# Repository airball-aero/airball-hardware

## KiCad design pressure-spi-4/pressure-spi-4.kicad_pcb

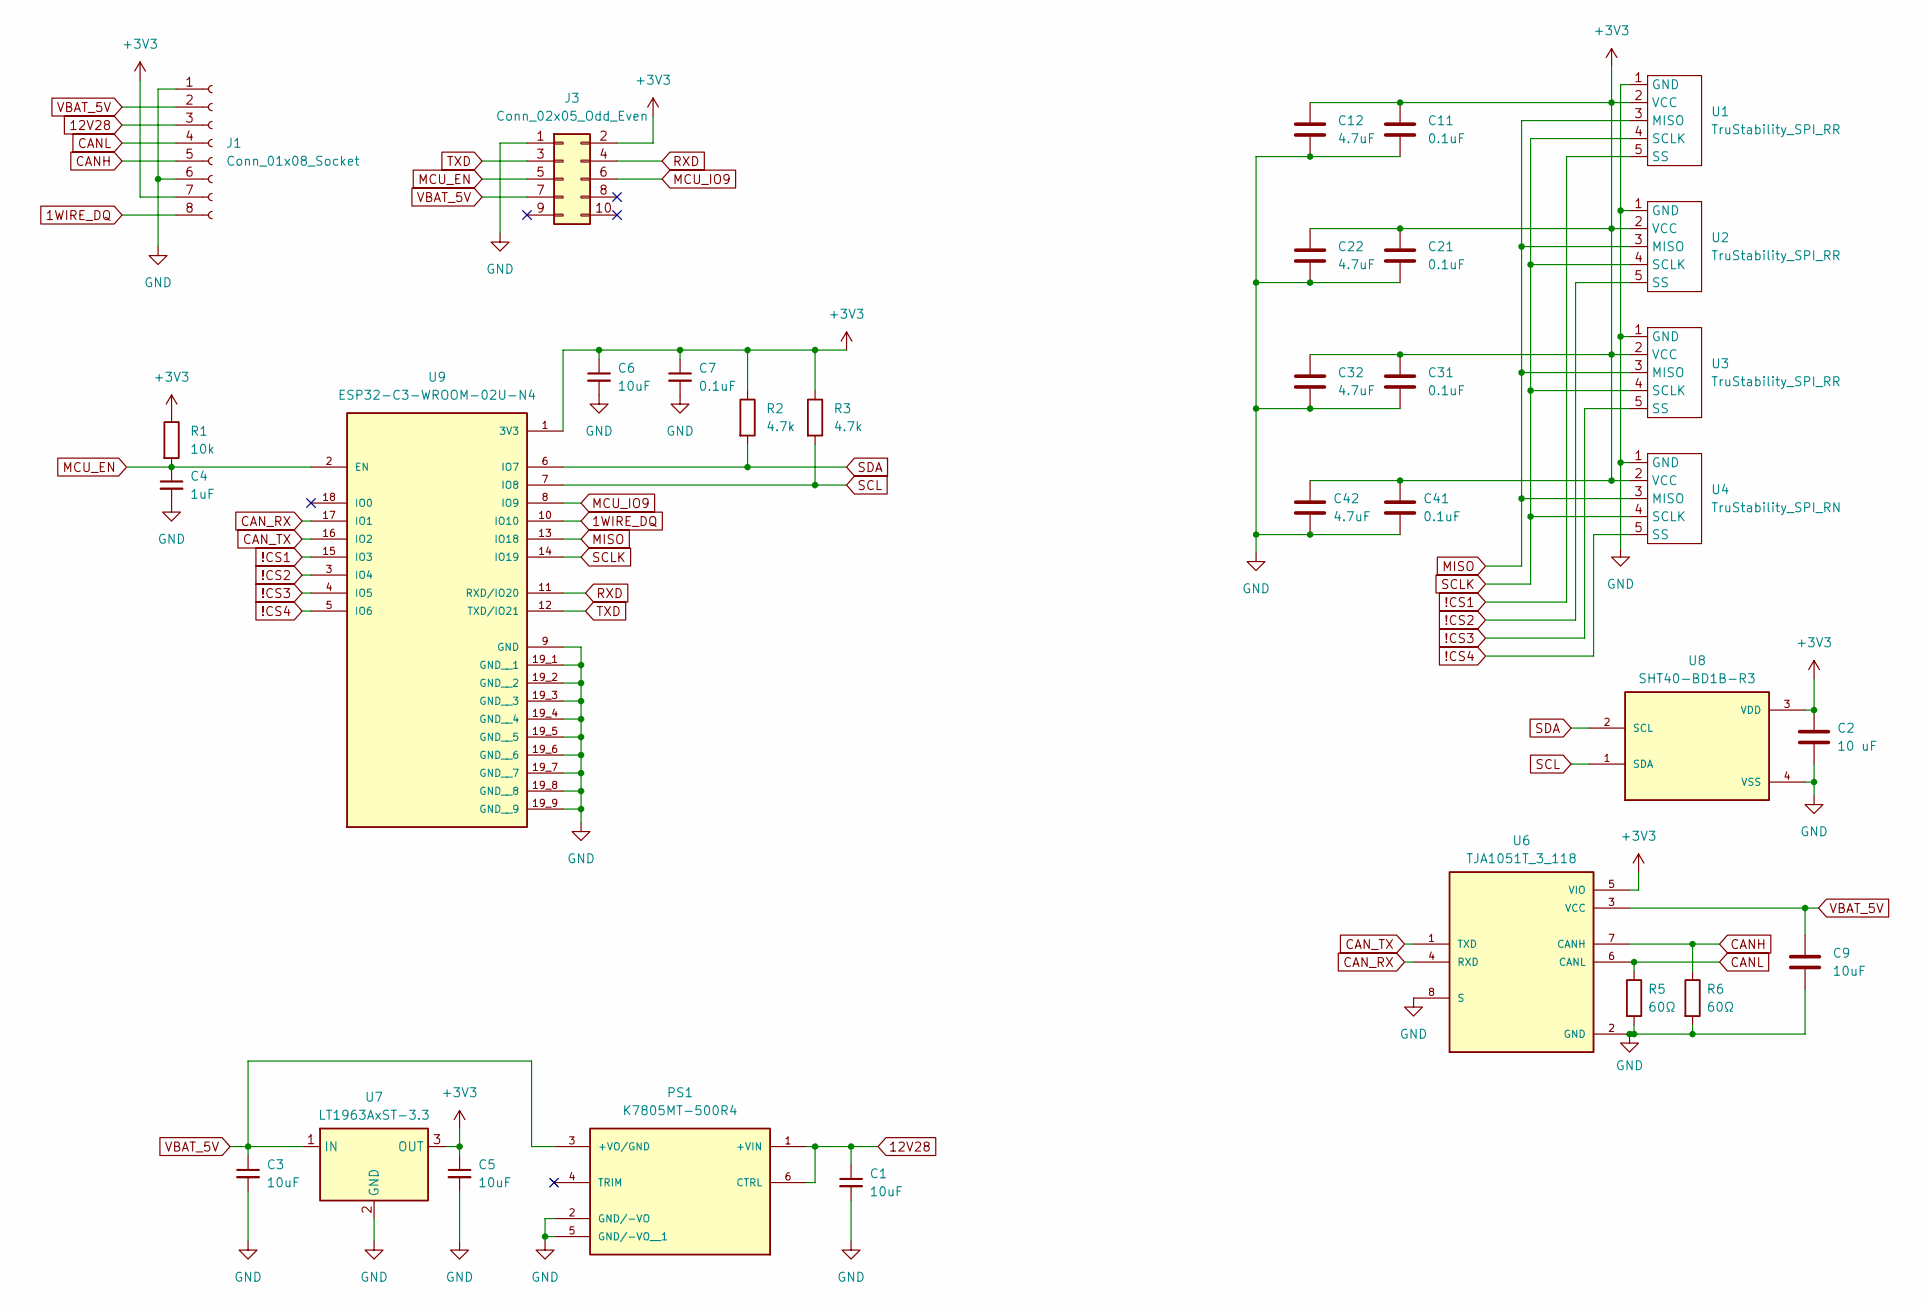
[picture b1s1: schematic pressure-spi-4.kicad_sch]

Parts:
C1, C3, C5, C6, C9: 10uF; C_0603_1608Metric
C2: 10 uF; C_0603_1608Metric
C4: 1uF; C_0603_1608Metric
C7, C11, C21, C31, C41: 0.1uF; C_0603_1608Metric
C12, C22, C32, C42: 4.7uF; C_0603_1608Metric
J1: Conn_01x08_Socket; PinHeader_1x08_P1.27mm_Vertical
J3: Conn_02x05_Odd_Even; PinHeader_2x05_P1.27mm_Vertical
PS1: K7805MT-500R4; CONV_K7805MT-500R4; PARTREV 2020.08.12-A/1
R1: 10k; R_0603_1608Metric
R2, R3: 4.7k; R_0603_1608Metric
R5, R6: 60Ω; R_0603_1608Metric
U1, U2, U3: TruStability_SPI_RR; TruStability SMT RR
U4: TruStability_SPI_RN; TruStability SMT RN
U6: TJA1051T_3_118; PARTREV 9
U7: LT1963AxST-3.3; SOT-223-3_TabPin2
U8: SHT40-BD1B-R3; SHT4X humidity sensor
U9: ESP32-C3-WROOM-02U-N4; XCVR_ESP32-C3-WROOM-02U-N4; PARTREV 1.3

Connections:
1WIRE_DQ: J1.8, U9.10 (IO10)
12V28: C1.1, J1.3, PS1.1 (+VIN), PS1.6 (CTRL)
!CS1: U1.5 (SS), U9.15 (IO3)
!CS2: U2.5 (SS), U9.3 (IO4)
!CS3: U3.5 (SS), U9.4 (IO5)
!CS4: U4.5 (SS), U9.5 (IO6)
+3V3: C2.1, C5.1, C6.1, C7.1, C11.1, C12.1, C21.1, C22.1, C31.1, C32.1, C41.1, C42.1, J1.7, J3.2, R1.1, R2.1, R3.1, U1.2 (VCC), U2.2 (VCC), U3.2 (VCC), U4.2 (VCC), U6.5 (VIO), U7.3 (OUT), U8.3 (VDD), U9.1 (3V3)
CANH: J1.5, R6.1, U6.7 (CANH)
CANL: J1.4, R5.1, U6.6 (CANL)
CAN_RX: U6.4 (RXD), U9.17 (IO1)
CAN_TX: U6.1 (TXD), U9.16 (IO2)
GND: C1.2, C2.2, C3.2, C4.2, C5.2, C6.2, C7.2, C9.2, C11.2, C12.2, C21.2, C22.2, C31.2, C32.2, C41.2, C42.2, J1.1, J1.6, J3.1, PS1.2 (GND/-VO), PS1.5 (GND/-VO__1), R5.2, R6.2, U1.1 (GND), U2.1 (GND), U3.1 (GND), U4.1 (GND), U6.2 (GND), U6.8 (S), U7.2 (GND), U8.4 (VSS), U9.9 (GND), U9.19_1 (GND__1), U9.19_2 (GND__2), U9.19_3 (GND__3), U9.19_4 (GND__4), U9.19_5 (GND__5), U9.19_6 (GND__6), U9.19_7 (GND__7), U9.19_8 (GND__8), U9.19_9 (GND__9), U9.20_1, U9.20_2, U9.20_3, U9.20_4, U9.20_5, U9.20_6, U9.20_7, U9.20_8, U9.20_9, U9.20_10, U9.20_11, U9.20_12
MCU_EN: C4.1, J3.5, R1.2, U9.2 (EN)
MCU_IO9: J3.6, U9.8 (IO9)
MISO: U1.3 (MISO), U2.3 (MISO), U3.3 (MISO), U4.3 (MISO), U9.13 (IO18)
RXD: J3.4, U9.11 (RXD/IO20)
SCL: R3.2, U8.1 (SDA), U9.7 (IO8)
SCLK: U1.4 (SCLK), U2.4 (SCLK), U3.4 (SCLK), U4.4 (SCLK), U9.14 (IO19)
SDA: R2.2, U8.2 (SCL), U9.6 (IO7)
TXD: J3.3, U9.12 (TXD/IO21)
VBAT_5V: C3.1, C9.1, J1.2, J3.7, PS1.3 (+VO/GND), U6.3 (VCC), U7.1 (IN)

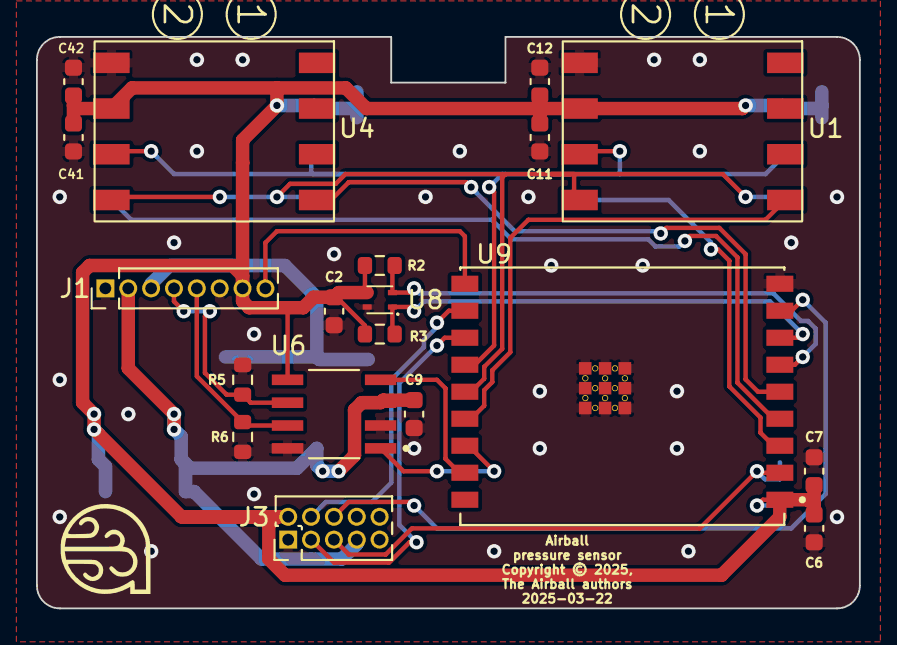
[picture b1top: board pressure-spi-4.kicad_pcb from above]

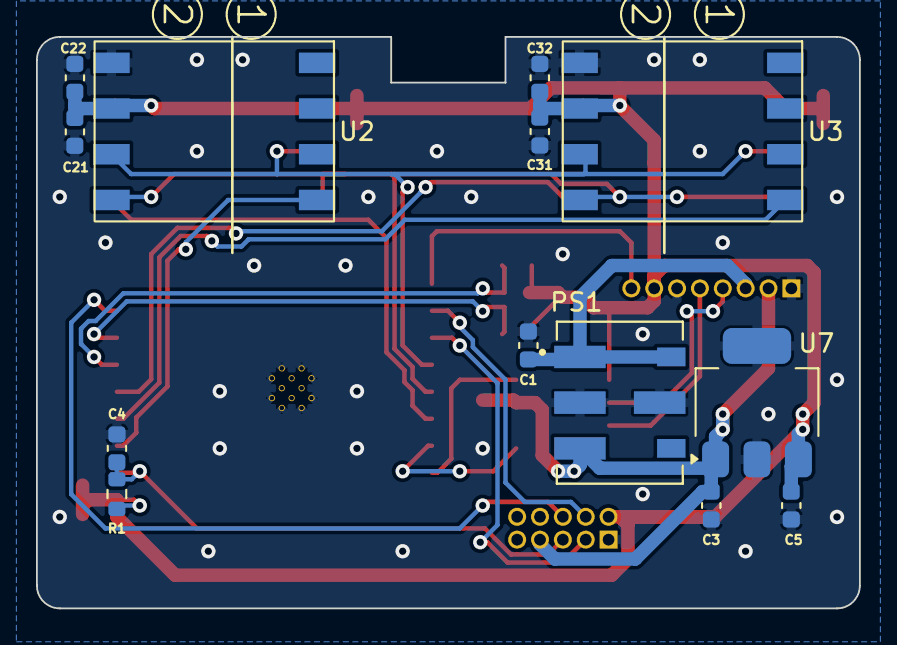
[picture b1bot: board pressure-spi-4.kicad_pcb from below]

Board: 2 copper layers, 45.7 x 31.8 mm, 32 parts (13 on the bottom side), 21 nets.

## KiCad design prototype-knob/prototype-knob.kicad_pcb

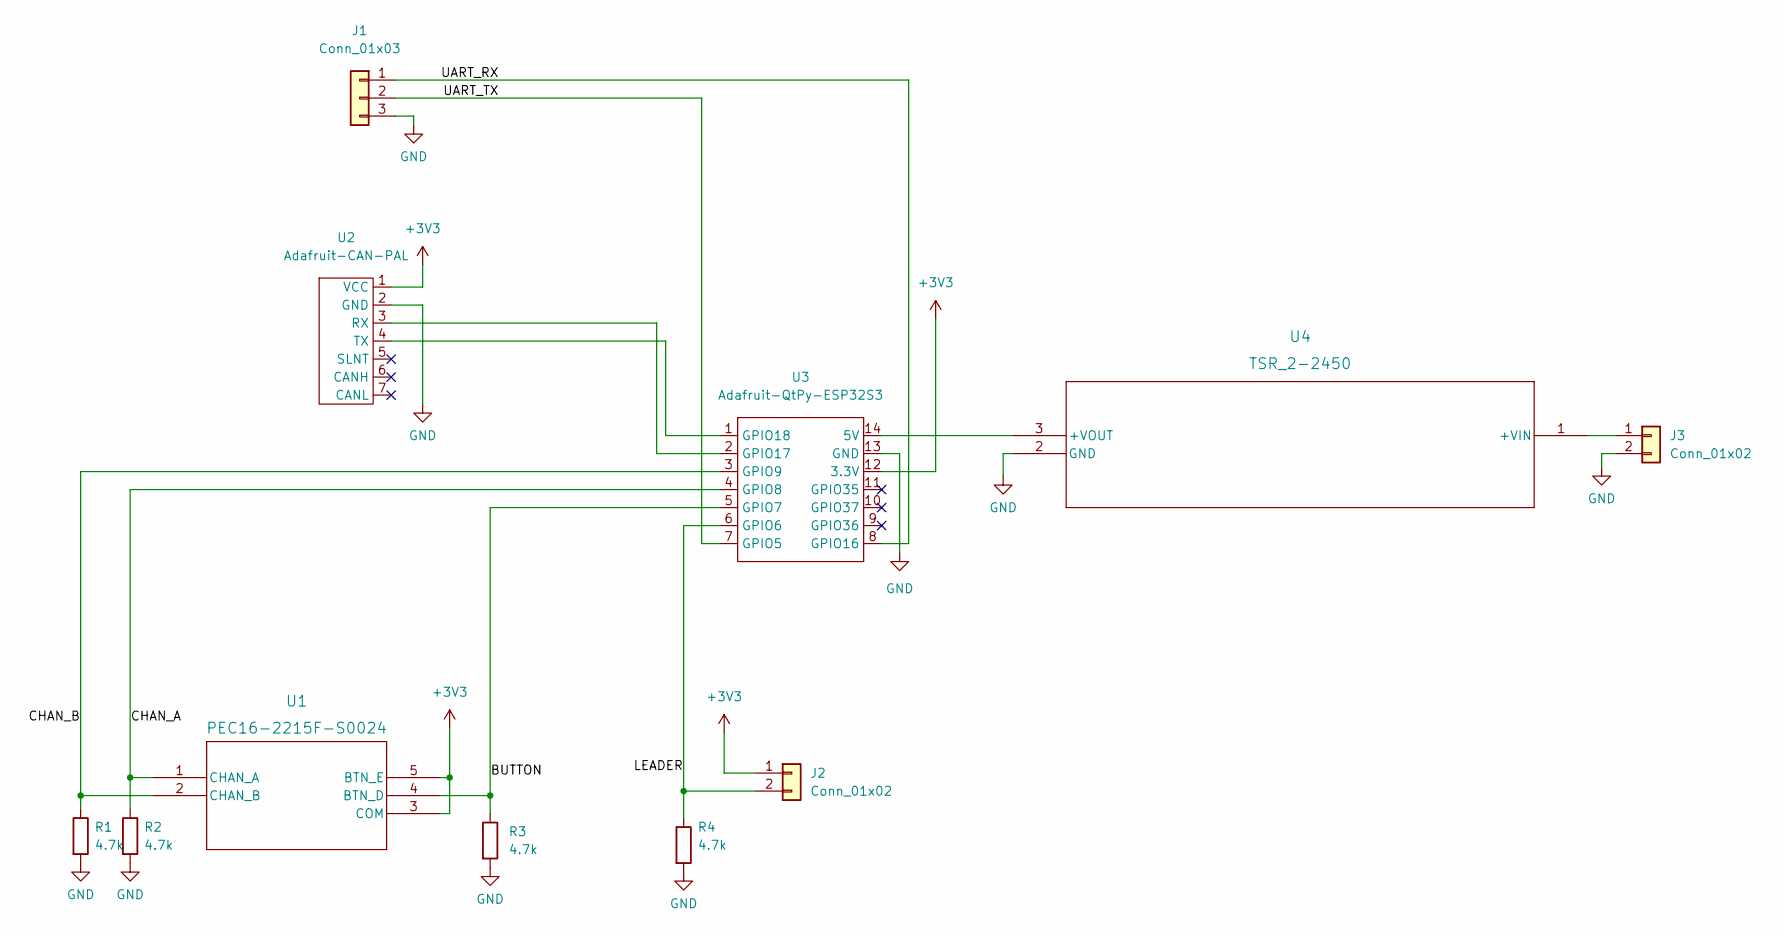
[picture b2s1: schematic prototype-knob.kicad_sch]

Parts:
J1: Conn_01x03; PinHeader_1x03_P2.54mm_Vertical
J2, J3: Conn_01x02; PinHeader_1x02_P2.54mm_Vertical
R1, R2, R3, R4: 4.7k; R_Axial_DIN0207_L6.3mm_D2.5mm_P10.16mm_Horizontal
U1: PEC16-2215F-S0024; PEC16-2215F_BRN
U2: Adafruit-CAN-PAL
U3: Adafruit-QtPy-ESP32S3
U4: TSR_2-2450; TSR 2-2450_TRP

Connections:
+3V3: J2.1, U1.3 (COM), U1.5 (BTN_E), U2.1 (VCC), U3.12 (3.3V)
/BUTTON: R3.1, U1.4 (BTN_D), U3.5 (GPIO7)
/CHAN_A: R2.1, U1.1 (CHAN_A), U3.4 (GPIO8)
/CHAN_B: R1.1, U1.2 (CHAN_B), U3.3 (GPIO9)
/LEADER: J2.2, R4.1, U3.6 (GPIO6)
/UART_RX: J1.1, U3.8 (GPIO16)
/UART_TX: J1.2, U3.7 (GPIO5)
GND: J1.3, J3.2, R1.2, R2.2, R3.2, R4.2, U2.2 (GND), U3.13 (GND), U4.2 (GND)
unnamed: J3.1, U4.1 (+VIN)
unnamed: U2.3 (RX), U3.2 (GPIO17)
unnamed: U2.4 (TX), U3.1 (GPIO18)
unnamed: U3.14 (5V), U4.3 (+VOUT)

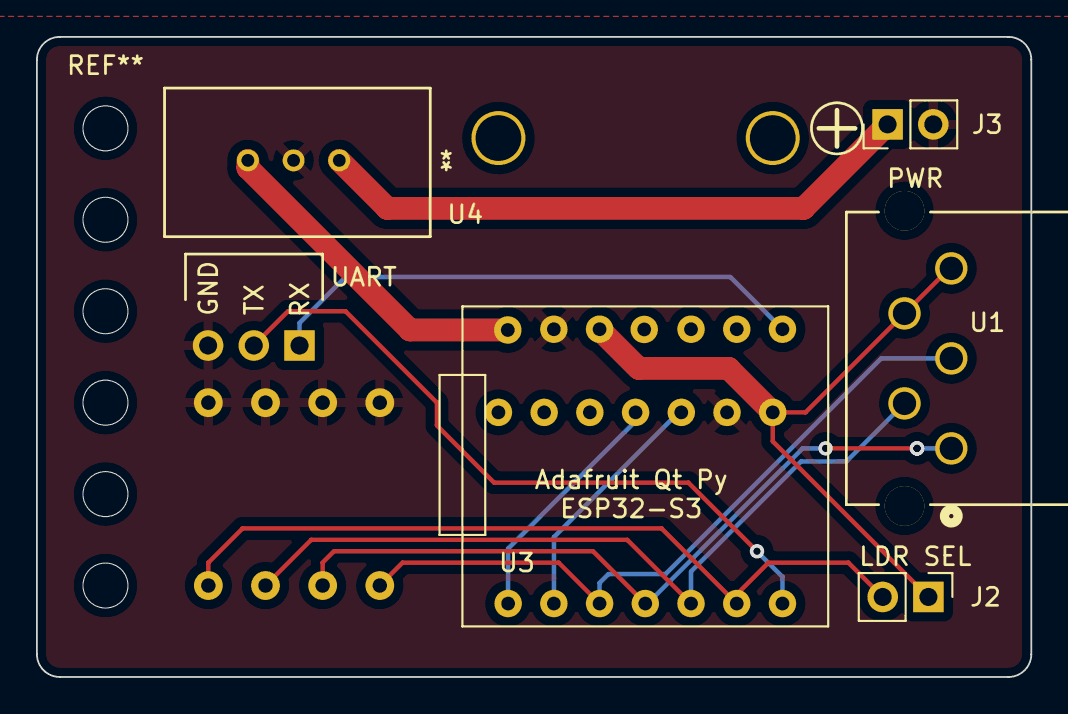
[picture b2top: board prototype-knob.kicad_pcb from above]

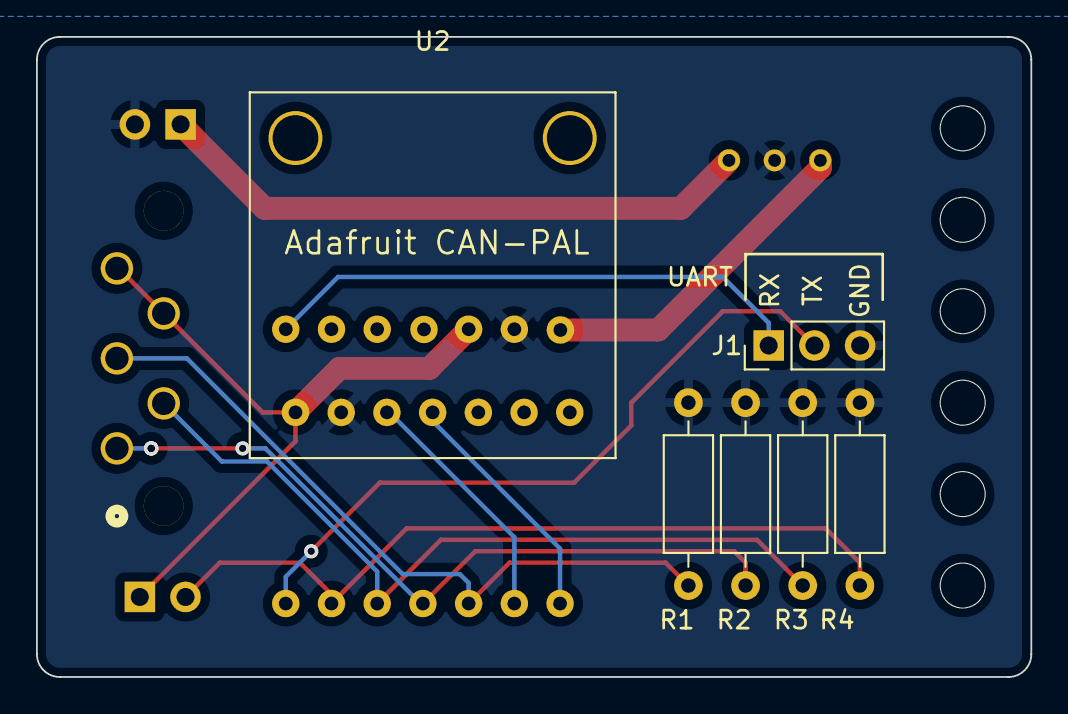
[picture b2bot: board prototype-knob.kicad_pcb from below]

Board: 2 copper layers, 55.2 x 35.6 mm, 11 parts (6 on the bottom side), 12 nets.

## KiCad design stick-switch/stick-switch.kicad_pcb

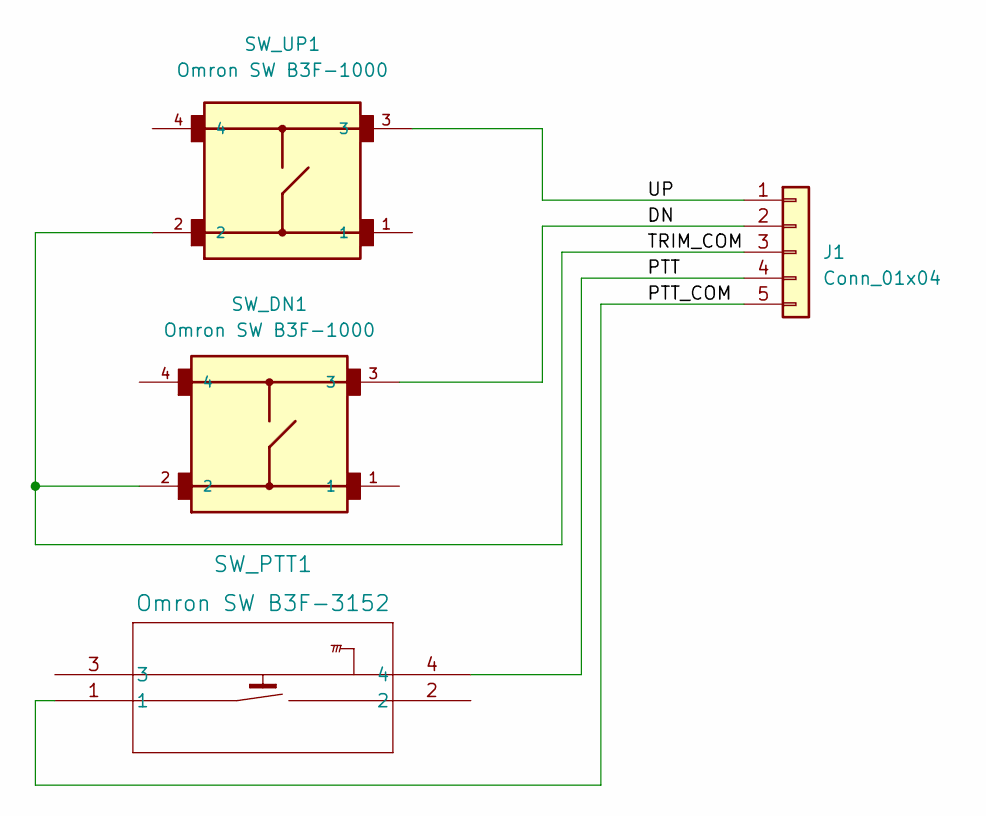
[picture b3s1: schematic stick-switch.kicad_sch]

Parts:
J1: Conn_01x04; PinHeader_1x05_P1.27mm_Vertical
SW_DN1: Omron SW B3F-1000
SW_PTT1: Omron SW B3F-3152
SW_UP1: Omron SW B3F-1000

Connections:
/DN: J1.2, SW_DN1.3
/PTT: J1.4, SW_PTT1.4
/PTT_COM: J1.5, SW_PTT1.1
/TRIM_COM: J1.3, SW_DN1.2, SW_UP1.2
/UP: J1.1, SW_UP1.3

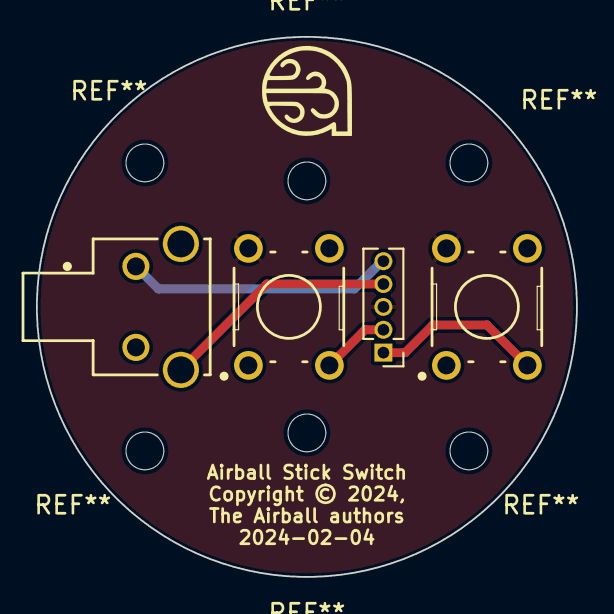
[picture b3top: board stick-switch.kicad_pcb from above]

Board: 2 copper layers, 30.0 x 30.0 mm, 4 parts (0 on the bottom side), 5 nets.

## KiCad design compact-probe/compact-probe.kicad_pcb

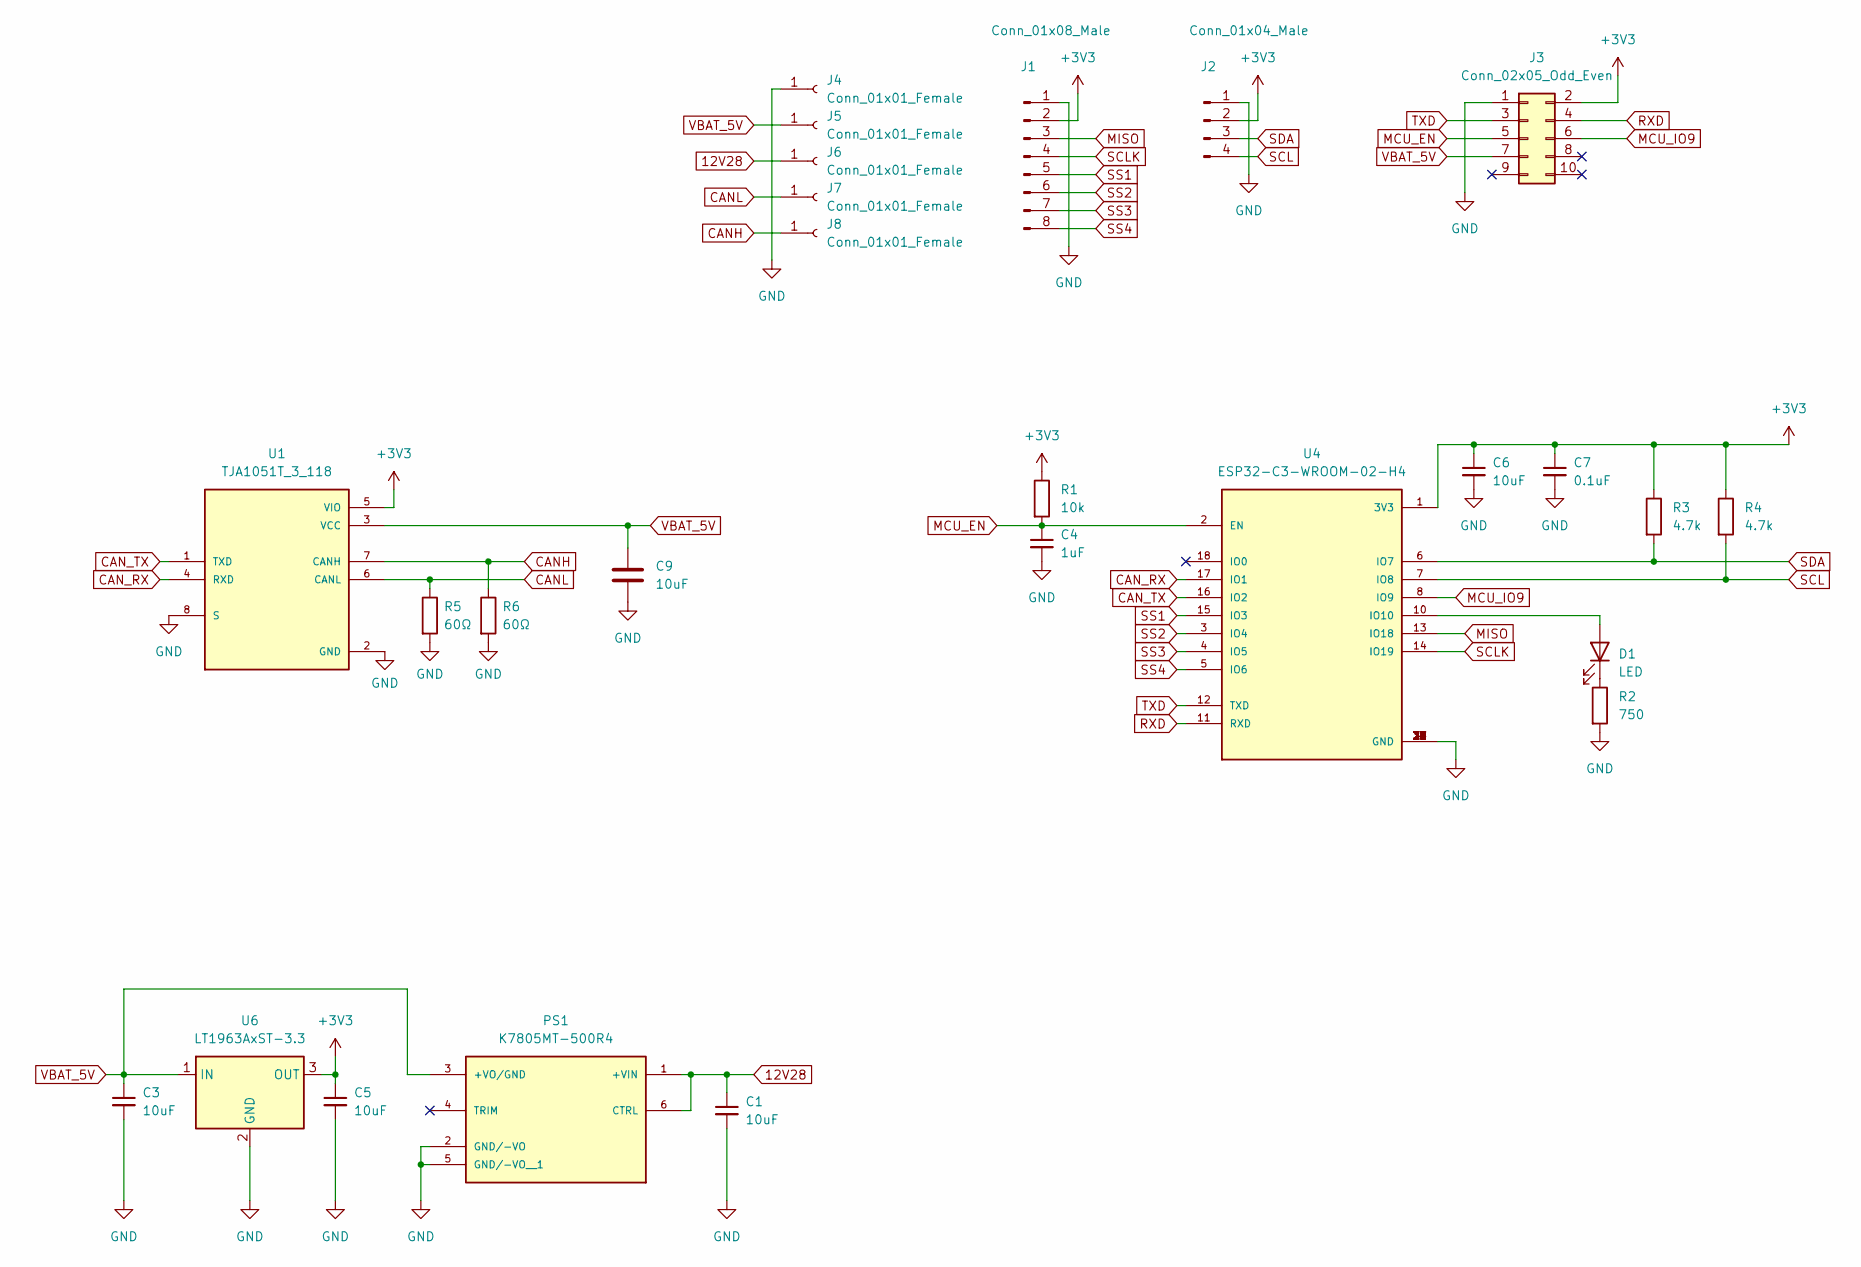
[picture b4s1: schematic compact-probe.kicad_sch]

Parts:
C1, C3, C5, C6, C9: 10uF; C_0603_1608Metric
C4: 1uF; C_0603_1608Metric
C7: 0.1uF; C_0603_1608Metric
D1: LED; LED_0603_1608Metric
J1: Conn_01x08_Male; JST_SH_SM08B-SRSS-TB_1x08-1MP_P1.00mm_Horizontal
J2: Conn_01x04_Male; JST_SM04B-SRSS-TB(LF)(SN)
J3: Conn_02x05_Odd_Even; PinHeader_2x05_P1.27mm_Vertical
J4, J5, J6, J7, J8: Conn_01x01_Female; SolderWirePad_1x01_SMD_1x2mm
PS1: K7805MT-500R4; CONV_K7805MT-500R4; PARTREV 2020.08.12-A/1
R1: 10k; R_0603_1608Metric
R2: 750; R_0603_1608Metric
R3, R4: 4.7k; R_0603_1608Metric
R5, R6: 60Ω; R_0603_1608Metric
U1: TJA1051T_3_118; PARTREV 9
U4: ESP32-C3-WROOM-02-H4; MODULE_ESP32-C3-WROOM-02-H4
U6: LT1963AxST-3.3; SOT-223-3_TabPin2

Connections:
12V28: C1.1, J6.1, PS1.1 (+VIN), PS1.6 (CTRL)
+3V3: C5.1, C6.1, C7.1, J1.2, J2.2, J3.2, R1.1, R3.1, R4.1, U1.5 (VIO), U4.1 (3V3), U6.3 (OUT)
CANH: J8.1, R6.1, U1.7 (CANH)
CANL: J7.1, R5.1, U1.6 (CANL)
CAN_RX: U1.4 (RXD), U4.17 (IO1)
CAN_TX: U1.1 (TXD), U4.16 (IO2)
GND: C1.2, C3.2, C4.2, C5.2, C6.2, C7.2, C9.2, J1.1, J2.1, J3.1, J4.1, PS1.2 (GND/-VO), PS1.5 (GND/-VO__1), R2.2, R5.2, R6.2, U1.2 (GND), U1.8 (S), U4.9 (GND), U4.19 (GND), U4.20 (GND), U4.21 (GND), U4.22 (GND), U4.23 (GND), U4.24 (GND), U4.25 (GND), U4.26 (GND), U4.27 (GND), U4.28 (GND), U4.29 (GND), U4.30 (GND), U4.31 (GND), U4.32 (GND), U4.33 (GND), U4.34 (GND), U4.35 (GND), U4.36 (GND), U4.37 (GND), U4.38 (GND), U4.39 (GND), U6.2 (GND)
MCU_EN: C4.1, J3.5, R1.2, U4.2 (EN)
MCU_IO9: J3.6, U4.8 (IO9)
MISO: J1.3, U4.13 (IO18)
unnamed: D1.1 (K), R2.1
unnamed: D1.2 (A), U4.10 (IO10)
RXD: J3.4, U4.11 (RXD)
SCL: J2.4, R4.2, U4.7 (IO8)
SCLK: J1.4, U4.14 (IO19)
SDA: J2.3, R3.2, U4.6 (IO7)
SS1: J1.5, U4.15 (IO3)
SS2: J1.6, U4.3 (IO4)
SS3: J1.7, U4.4 (IO5)
SS4: J1.8, U4.5 (IO6)
TXD: J3.3, U4.12 (TXD)
VBAT_5V: C3.1, C9.1, J3.7, J5.1, PS1.3 (+VO/GND), U1.3 (VCC), U6.1 (IN)

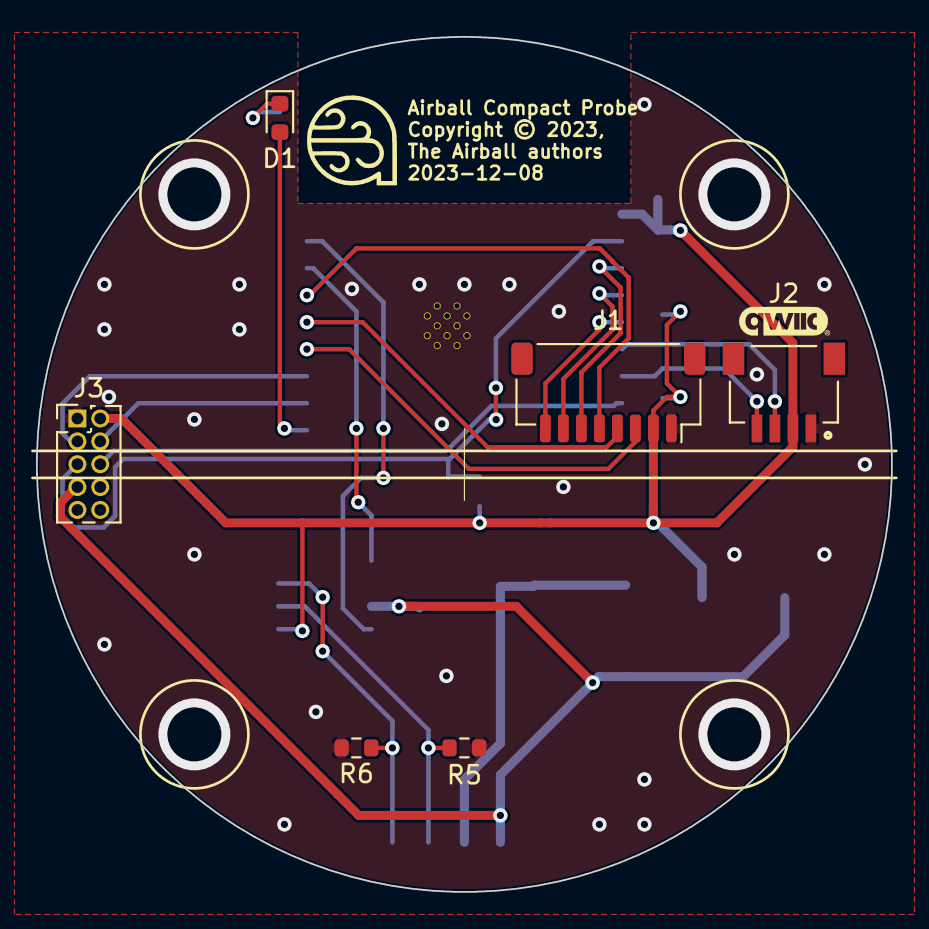
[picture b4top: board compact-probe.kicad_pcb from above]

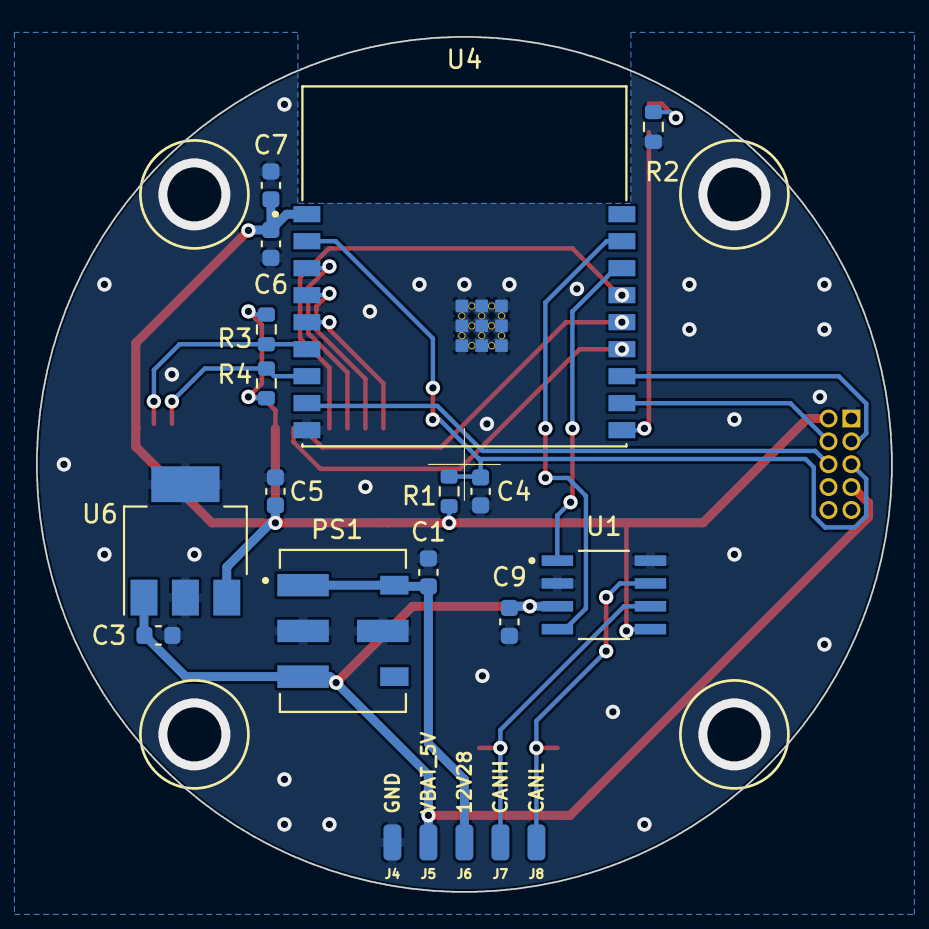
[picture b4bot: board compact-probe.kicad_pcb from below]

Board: 2 copper layers, 47.5 x 47.5 mm, 26 parts (20 on the bottom side), 22 nets.

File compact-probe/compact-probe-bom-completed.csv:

Id,Designator,Package,Quantity,Designation,Supplier and ref
1,D1,LED_0603_1608Metric,1,LED,Standard part
2,"R6,R5",R_0603_1608Metric,2,60Ω,Standard part
3,J2,JST_SM04B-SRSS-TB(LF)(SN),1,Conn_01x04_Male,https://www.digikey.com/en/products/detail/jst-sales-america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
4,J3,PinHeader_2x05_P1.27mm_Vertical,1,Conn_02x05_Odd_Even,DO NOT POPULATE
5,J1,JST_SH_SM08B-SRSS-TB_1x08-1MP_P1.00mm_Horizontal,1,Conn_01x08_Male,https://www.digikey.com/en/products/detail/jst-sales-america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
6,"C9,C5,C1,C6,C3",C_0603_1608Metric,5,10uF,Standard part
7,U6,SOT-223-3_TabPin2,1,LT1963AxST-3.3,https://www.digikey.com/en/products/detail/analog-devices-in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
8,"J6,J5,J4,J8,J7",SolderWirePad_1x01_SMD_1x2mm,5,Conn_01x01_Female,DO NOT POPULATE
9,U1,TJA1051T_3_118,1,TJA1051T_3_118,https://www.digikey.com/en/products/detail/nxp-usa-inc/TJA10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
10,"R4,R3",R_0603_1608Metric,2,4.7k,Standard part
11,R1,R_0603_1608Metric,1,10k,Standard part
12,C7,C_0603_1608Metric,1,0.1uF,Standard part
13,R2,R_0603_1608Metric,1,750,Standard part
14,U4,MODULE_ESP32-C3-WROOM-02-H4,1,ESP32-C3-WROOM-02-H4,https://www.mouser.com/ProductDetail/Espressif-Systems/ESP32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
15,PS1,CONV_K7805MT-500R4,1,K7805MT-500R4,https://www.digikey.com/en/products/detail/mornsun-america-l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
16,C4,C_0603_1608Metric,1,1uF,Standard part

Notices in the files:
baro-temp-qwiic/baro-temp-qwiic.kicad_pcb:
Copyright © 2023,
The Airball authors
pressure-qwiic-3/pressure-qwiic-3.kicad_pcb:
Copyright (C) 2023,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
pressure-spi-4/pressure-spi-4.kicad_pcb:
Copyright © 2025,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
small-display/small-display.kicad_sch:
© 2020-2022 Raspberry Pi Ltd (formerly Raspberry Pi (Trading) Ltd.)
stick-switch/stick-switch.kicad_pcb:
Copyright © 2024,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
parts and their libraries:
Copyright 2021 Accelerated Designs. All rights reserved.
